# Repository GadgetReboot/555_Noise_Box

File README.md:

# 555_Noise_Box
Dual 555 oscillators with Flip Flop sub-oscillators controlled by MCP42100 digital pots to make sound effects or melodies
<br><br><BR><BR>

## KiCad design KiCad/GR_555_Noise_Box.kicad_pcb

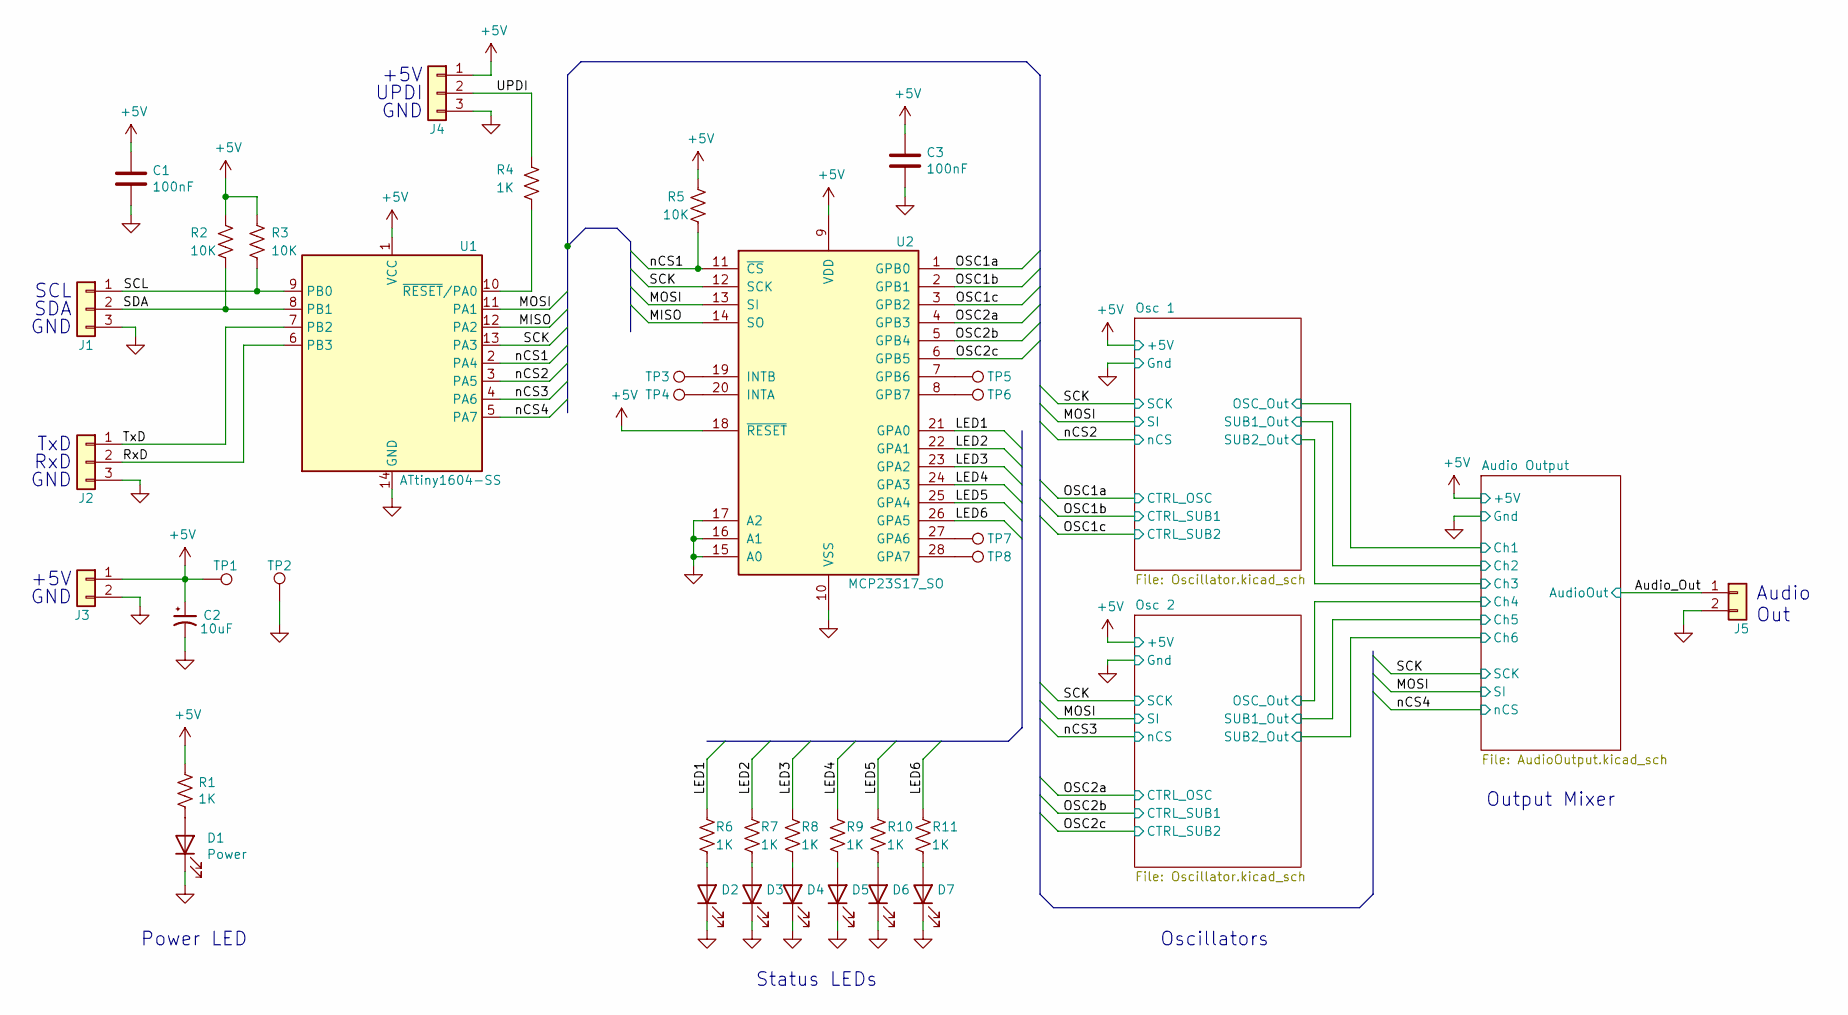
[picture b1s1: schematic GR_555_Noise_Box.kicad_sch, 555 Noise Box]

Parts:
C1, C3: 100nF; C_0805_2012Metric_Pad1.15x1.40mm_HandSolder
C2: 10uF; C_Elec_4x5.8
D1: Power; LED_0805_2012Metric_Pad1.15x1.40mm_HandSolder
D2, D3, D4, D5, D6, D7: LED; LED_0805_2012Metric_Pad1.15x1.40mm_HandSolder
J1, J2, J4: Conn_01x03; PinHeader_1x03_P2.54mm_Vertical_H1.0mm
J3, J5: 1x2; PinHeader_1x02_P2.54mm_Vertical_H1.0mm
R1, R4, R6, R7, R8, R9, R10, R11: 1K; R_0805_2012Metric_Pad1.15x1.40mm_HandSolder
R2, R3, R5: 10K; R_0805_2012Metric_Pad1.15x1.40mm_HandSolder
TP1, TP2: TestPoint; TestPoint_Loop_D2.54mm_Drill1.5mm_Beaded
TP3, TP4, TP5, TP6, TP7, TP8: TestPoint; TestPoint_Pad_D1.0mm
U1: ATtiny1604-SS; SOIC-14_3.9x8.7mm_P1.27mm
U2: MCP23S17_SO; SOIC-28W_7.5x17.9mm_P1.27mm

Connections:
+5V: C1.1, C2.1, C3.1, J3.1, J4.1, R1.1, R2.1, R3.1, R5.1, TP1.1, U1.1 (VCC), U2.9 (VDD), U2.18 (~RESET); also elsewhere on the board
/Audio_Out: J5.1; also elsewhere on the board
/LED1: R6.2, U2.21 (GPA0)
/LED2: R7.2, U2.22 (GPA1)
/LED3: R8.2, U2.23 (GPA2)
/LED4: R9.2, U2.24 (GPA3)
/LED5: R10.2, U2.25 (GPA4)
/LED6: R11.2, U2.26 (GPA5)
/MISO: U1.12 (PA2), U2.14 (SO)
/MOSI: U1.11 (PA1), U2.13 (SI); also elsewhere on the board
/OSC1a: U2.1 (GPB0); also elsewhere on the board
/OSC1b: U2.2 (GPB1); also elsewhere on the board
/OSC1c: U2.3 (GPB2); also elsewhere on the board
/OSC2a: U2.4 (GPB3); also elsewhere on the board
/OSC2b: U2.5 (GPB4); also elsewhere on the board
/OSC2c: U2.6 (GPB5); also elsewhere on the board
/RxD: J2.2, U1.6 (PB3)
/SCK: U1.13 (PA3), U2.12 (SCK); also elsewhere on the board
/SCL: J1.1, R3.2, U1.9 (PB0)
/SDA: J1.2, R2.2, U1.8 (PB1)
/TxD: J2.1, U1.7 (PB2)
/UPDI: J4.2, R4.1
/nCS1: R5.2, U1.2 (PA4), U2.11 (~CS)
/nCS2: U1.3 (PA5); also elsewhere on the board
/nCS3: U1.4 (PA6); also elsewhere on the board
/nCS4: U1.5 (PA7); also elsewhere on the board
GND: C1.2, C2.2, C3.2, D1.1 (K), D2.1 (K), D3.1 (K), D4.1 (K), D5.1 (K), D6.1 (K), D7.1 (K), J1.3, J2.3, J3.2, J4.3, J5.2, TP2.1, U1.14 (GND), U2.10 (VSS), U2.15 (A0), U2.16 (A1), U2.17 (A2); also elsewhere on the board
unnamed: D1.2 (A), R1.2
unnamed: D2.2 (A), R6.1
unnamed: D3.2 (A), R7.1
unnamed: D4.2 (A), R8.1
unnamed: D5.2 (A), R9.1
unnamed: D6.2 (A), R10.1
unnamed: D7.2 (A), R11.1
unnamed: R4.2, U1.10 (~RESET/PA0)
unnamed: TP3.1, U2.19 (INTB)
unnamed: TP4.1, U2.20 (INTA)
unnamed: TP5.1, U2.7 (GPB6)
unnamed: TP6.1, U2.8 (GPB7)
unnamed: TP7.1, U2.27 (GPA6)
unnamed: TP8.1, U2.28 (GPA7)

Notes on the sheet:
UPDI
GND
RxD
Output Mixer
+5V
SDA
Oscillators
Power LED
Status LEDs
TxD
Audio Out
SCL

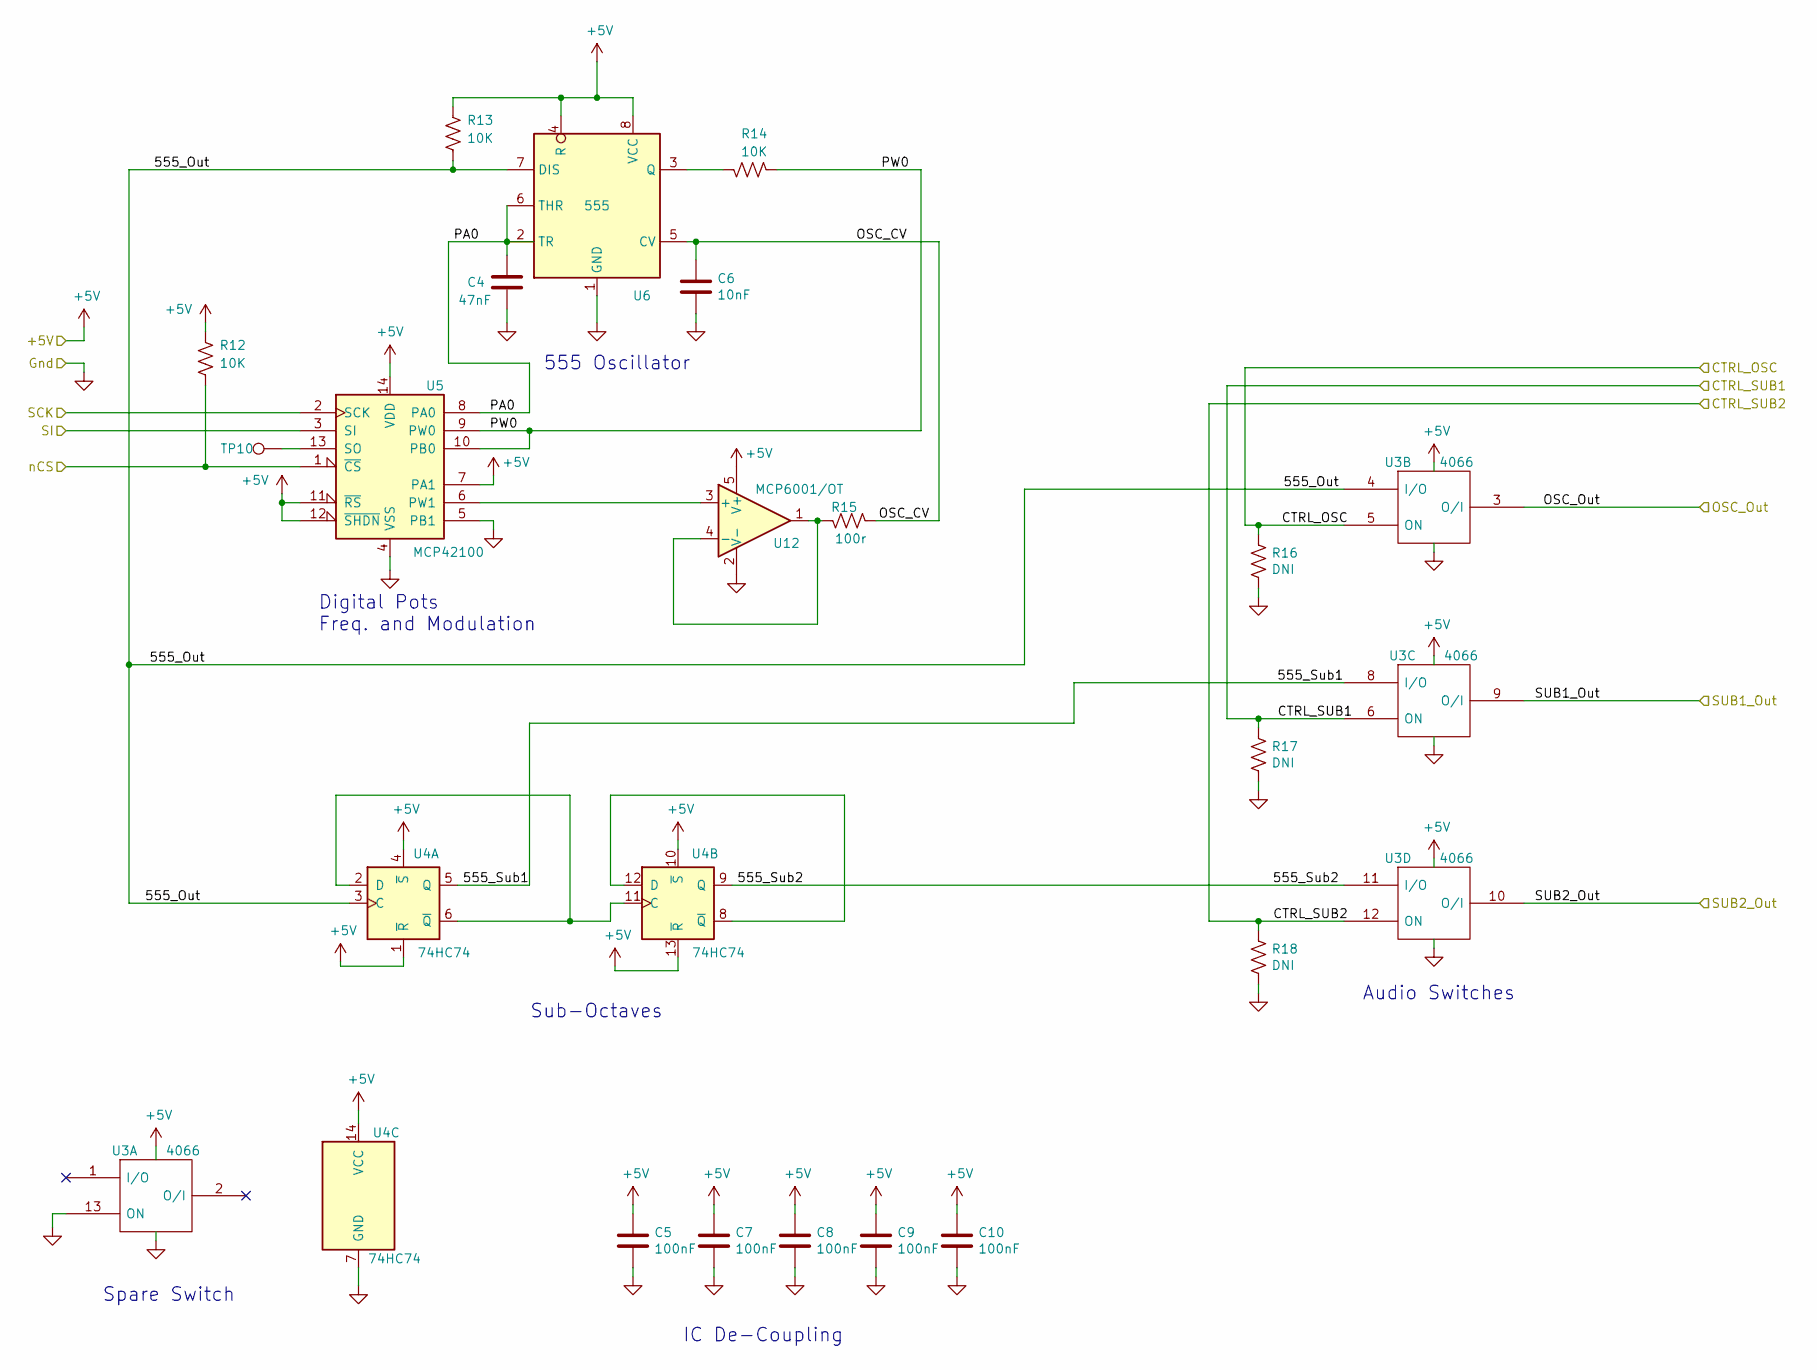
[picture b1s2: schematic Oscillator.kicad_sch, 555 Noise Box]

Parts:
C4: 47nF; C_0805_2012Metric_Pad1.15x1.40mm_HandSolder
C5, C7, C8, C9, C10: 100nF; C_0805_2012Metric_Pad1.15x1.40mm_HandSolder
C6: 10nF; C_0805_2012Metric_Pad1.15x1.40mm_HandSolder
R12, R13, R14: 10K; R_0805_2012Metric_Pad1.15x1.40mm_HandSolder
R15: 100r; R_0805_2012Metric_Pad1.15x1.40mm_HandSolder
R16, R17, R18: DNI; R_0805_2012Metric_Pad1.15x1.40mm_HandSolder
TP10: TestPoint; TestPoint_Pad_D1.0mm
U3: 4066; SOIC-14_3.9x8.7mm_P1.27mm
U4: 74HC74; SOIC-14_3.9x8.7mm_P1.27mm
U5: MCP42100; SOIC-14_3.9x8.7mm_P1.27mm
U6: 555; SOIC-8_3.9x4.9mm_P1.27mm
U12: MCP6001/OT; SOT-23-5

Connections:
+5V: C5.1, C7.1, C8.1, C9.1, C10.1, R12.1, R13.1, U3.14 (Vdd), U4.1 (~R), U4.4 (~S), U4.10 (~S), U4.13 (~R), U4.14 (VCC), U5.7 (PA1), U5.11 (~RS), U5.12 (~SHDN), U5.14 (VDD), U6.4 (R), U6.8 (VCC), U12.5 (V+); also elsewhere on the board
/Audio Output/Ch1: U3.3 (O/I); also elsewhere on the board
/Audio Output/Ch2: U3.9 (O/I); also elsewhere on the board
/Audio Output/Ch3: U3.10 (O/I); also elsewhere on the board
/MOSI: U5.3 (SI); also elsewhere on the board
/OSC1a: R16.1, U3.5 (ON); also elsewhere on the board
/OSC1b: R17.1, U3.6 (ON); also elsewhere on the board
/OSC1c: R18.1, U3.12 (ON); also elsewhere on the board
/Osc 1/555_Out: R13.2, U3.4 (I/O), U4.3 (C), U6.7 (DIS)
/Osc 1/555_Sub1: U3.8 (I/O), U4.5 (Q)
/Osc 1/555_Sub2: U3.11 (I/O), U4.9 (Q)
/Osc 1/OSC_CV: C6.1, R15.2, U6.5 (CV)
/Osc 1/PA0: C4.1, U5.8 (PA0), U6.2 (TR), U6.6 (THR)
/Osc 1/PW0: R14.2, U5.9 (PW0), U5.10 (PB0)
/SCK: U5.2 (SCK); also elsewhere on the board
/nCS2: R12.2, U5.1 (~CS); also elsewhere on the board
GND: C4.2, C5.2, C6.2, C7.2, C8.2, C9.2, C10.2, R16.2, R17.2, R18.2, U3.7 (Vss), U3.13 (ON), U4.7 (GND), U5.4 (VSS), U5.5 (PB1), U6.1 (GND), U12.2 (V-); also elsewhere on the board
unnamed: R14.1, U6.3 (Q)
unnamed: U4.2 (D), U4.6 (~Q), U4.11 (C)
unnamed: U4.8 (~Q), U4.12 (D)

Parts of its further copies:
C11: 47nF; C_0805_2012Metric_Pad1.15x1.40mm_HandSolder
C12, C14, C15, C16, C17: 100nF; C_0805_2012Metric_Pad1.15x1.40mm_HandSolder
C13: 10nF; C_0805_2012Metric_Pad1.15x1.40mm_HandSolder
R19, R20, R21: 10K; R_0805_2012Metric_Pad1.15x1.40mm_HandSolder
R22: 100r; R_0805_2012Metric_Pad1.15x1.40mm_HandSolder
R23, R24, R25: DNI; R_0805_2012Metric_Pad1.15x1.40mm_HandSolder
TP9: TestPoint; TestPoint_Pad_D1.0mm
U7: MCP6001/OT; SOT-23-5
U8: 4066; SOIC-14_3.9x8.7mm_P1.27mm
U9: 74HC74; SOIC-14_3.9x8.7mm_P1.27mm
U10: MCP42100; SOIC-14_3.9x8.7mm_P1.27mm
U11: 555; SOIC-8_3.9x4.9mm_P1.27mm

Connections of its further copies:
+5V: C12.1, C14.1, C15.1, C16.1, C17.1, R19.1, R20.1, U7.5 (V+), U8.14 (Vdd), U9.1 (~R), U9.4 (~S), U9.10 (~S), U9.13 (~R), U9.14 (VCC), U10.7 (PA1), U10.11 (~RS), U10.12 (~SHDN), U10.14 (VDD), U11.4 (R), U11.8 (VCC); also elsewhere on the board
/Audio Output/Ch4: U8.3 (O/I); also elsewhere on the board
/Audio Output/Ch5: U8.9 (O/I); also elsewhere on the board
/Audio Output/Ch6: U8.10 (O/I); also elsewhere on the board
/MOSI: U10.3 (SI); also elsewhere on the board
/OSC2a: R23.1, U8.5 (ON); also elsewhere on the board
/OSC2b: R24.1, U8.6 (ON); also elsewhere on the board
/OSC2c: R25.1, U8.12 (ON); also elsewhere on the board
/Osc 2/555_Out: R20.2, U8.4 (I/O), U9.3 (C), U11.7 (DIS)
/Osc 2/555_Sub1: U8.8 (I/O), U9.5 (Q)
/Osc 2/555_Sub2: U8.11 (I/O), U9.9 (Q)
/Osc 2/OSC_CV: C13.1, R22.2, U11.5 (CV)
/Osc 2/PA0: C11.1, U10.8 (PA0), U11.2 (TR), U11.6 (THR)
/Osc 2/PW0: R21.2, U10.9 (PW0), U10.10 (PB0)
/SCK: U10.2 (SCK); also elsewhere on the board
/nCS3: R19.2, U10.1 (~CS); also elsewhere on the board
GND: C11.2, C12.2, C13.2, C14.2, C15.2, C16.2, C17.2, R23.2, R24.2, R25.2, U7.2 (V-), U8.7 (Vss), U8.13 (ON), U9.7 (GND), U10.4 (VSS), U10.5 (PB1), U11.1 (GND); also elsewhere on the board
unnamed: R21.1, U11.3 (Q)
unnamed: U9.2 (D), U9.6 (~Q), U9.11 (C)
unnamed: U9.8 (~Q), U9.12 (D)

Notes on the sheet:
Audio Switches
Sub-Octaves
Spare Switch
555 Oscillator
Digital Pots Freq. and Modulation
IC De-Coupling

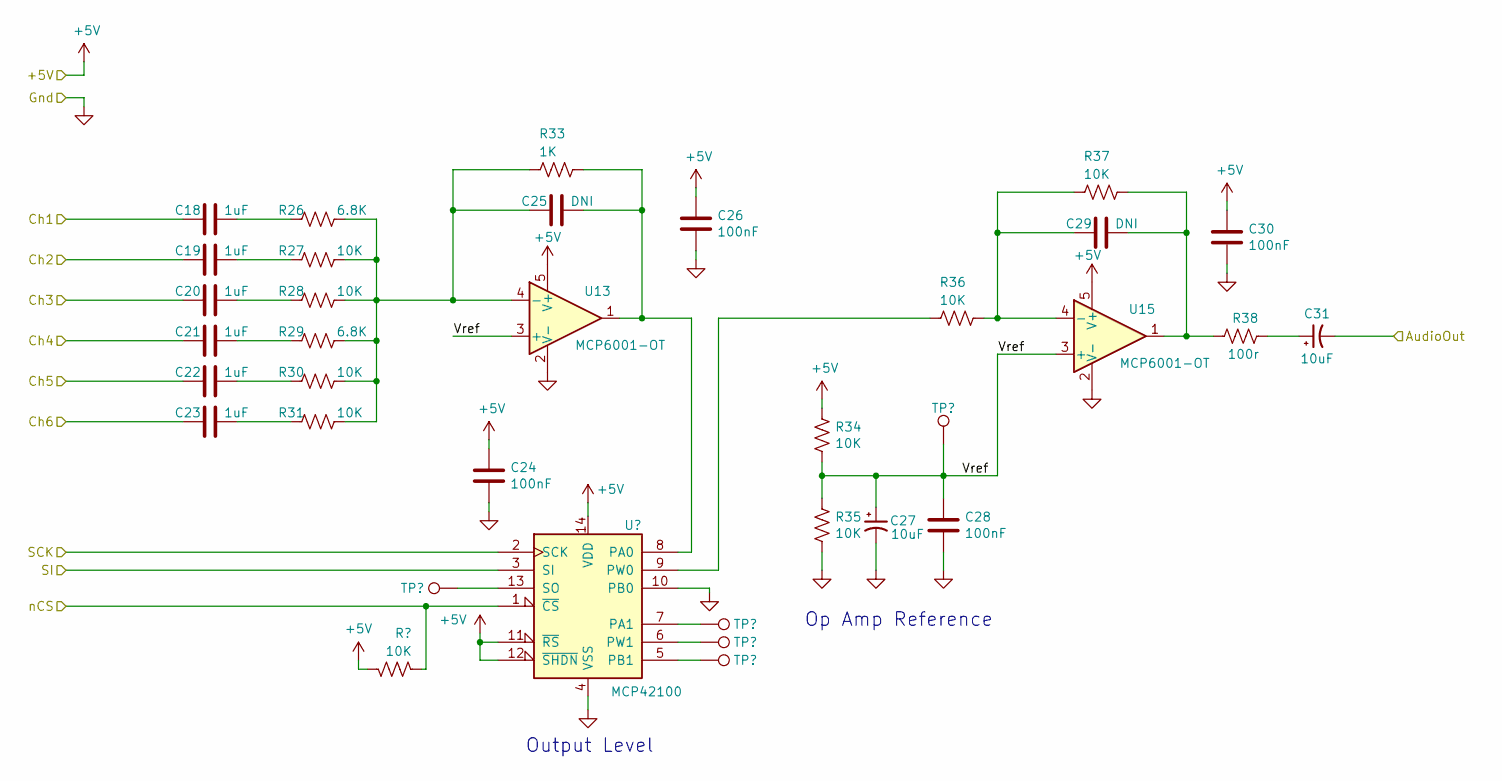
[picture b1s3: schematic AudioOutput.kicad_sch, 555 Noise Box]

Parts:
C18, C19, C20, C21, C22, C23: 1uF; C_0805_2012Metric_Pad1.15x1.40mm_HandSolder
C24, C26, C28, C30: 100nF; C_0805_2012Metric_Pad1.15x1.40mm_HandSolder
C25, C29: DNI; C_0805_2012Metric_Pad1.15x1.40mm_HandSolder
C27, C31: 10uF; C_Elec_4x5.8
R26, R29: 6.8K; R_0805_2012Metric_Pad1.15x1.40mm_HandSolder
R27, R28, R30, R31, R32, R34, R35, R36, R37: 10K; R_0805_2012Metric_Pad1.15x1.40mm_HandSolder
R33: 1K; R_0805_2012Metric_Pad1.15x1.40mm_HandSolder
R38: 100r; R_0805_2012Metric_Pad1.15x1.40mm_HandSolder
TP11, TP12, TP13, TP14, TP15: TestPoint; TestPoint_Pad_D1.0mm
U13, U15: MCP6001-OT; SOT-23-5
U14: MCP42100; SOIC-14_3.9x8.7mm_P1.27mm

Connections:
+5V: C24.1, C26.1, C30.1, R32.1, R34.1, U13.5 (V+), U14.11 (~RS), U14.12 (~SHDN), U14.14 (VDD), U15.5 (V+); also elsewhere on the board
/Audio Output/Ch1: C18.2; also elsewhere on the board
/Audio Output/Ch2: C19.2; also elsewhere on the board
/Audio Output/Ch3: C20.2; also elsewhere on the board
/Audio Output/Ch4: C21.2; also elsewhere on the board
/Audio Output/Ch5: C22.2; also elsewhere on the board
/Audio Output/Ch6: C23.2; also elsewhere on the board
/Audio Output/Vref: C27.1, C28.1, R34.2, R35.1, TP15.1, U13.3 (+), U15.3 (+)
/Audio_Out: C31.2; also elsewhere on the board
/MOSI: U14.3 (SI); also elsewhere on the board
/SCK: U14.2 (SCK); also elsewhere on the board
/nCS4: R32.2, U14.1 (~CS); also elsewhere on the board
GND: C24.2, C26.2, C27.2, C28.2, C30.2, R35.2, U13.2 (V-), U14.4 (VSS), U14.10 (PB0), U15.2 (V-); also elsewhere on the board
unnamed: C18.1, R26.2
unnamed: C19.1, R27.2
unnamed: C20.1, R28.2
unnamed: C21.1, R29.2
unnamed: C22.1, R30.2
unnamed: C23.1, R31.2
unnamed: C25.1, R33.1, U13.1, U14.8 (PA0)
unnamed: C25.2, R26.1, R27.1, R28.1, R29.1, R30.1, R31.1, R33.2, U13.4 (-)
unnamed: C29.1, R37.1, R38.2, U15.1
unnamed: C29.2, R36.1, R37.2, U15.4 (-)
unnamed: C31.1, R38.1
unnamed: R36.2, U14.9 (PW0)
unnamed: TP11.1, U14.13 (SO)
unnamed: TP12.1, U14.7 (PA1)
unnamed: TP13.1, U14.6 (PW1)
unnamed: TP14.1, U14.5 (PB1)

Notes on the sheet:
Output Level
Op Amp Reference

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
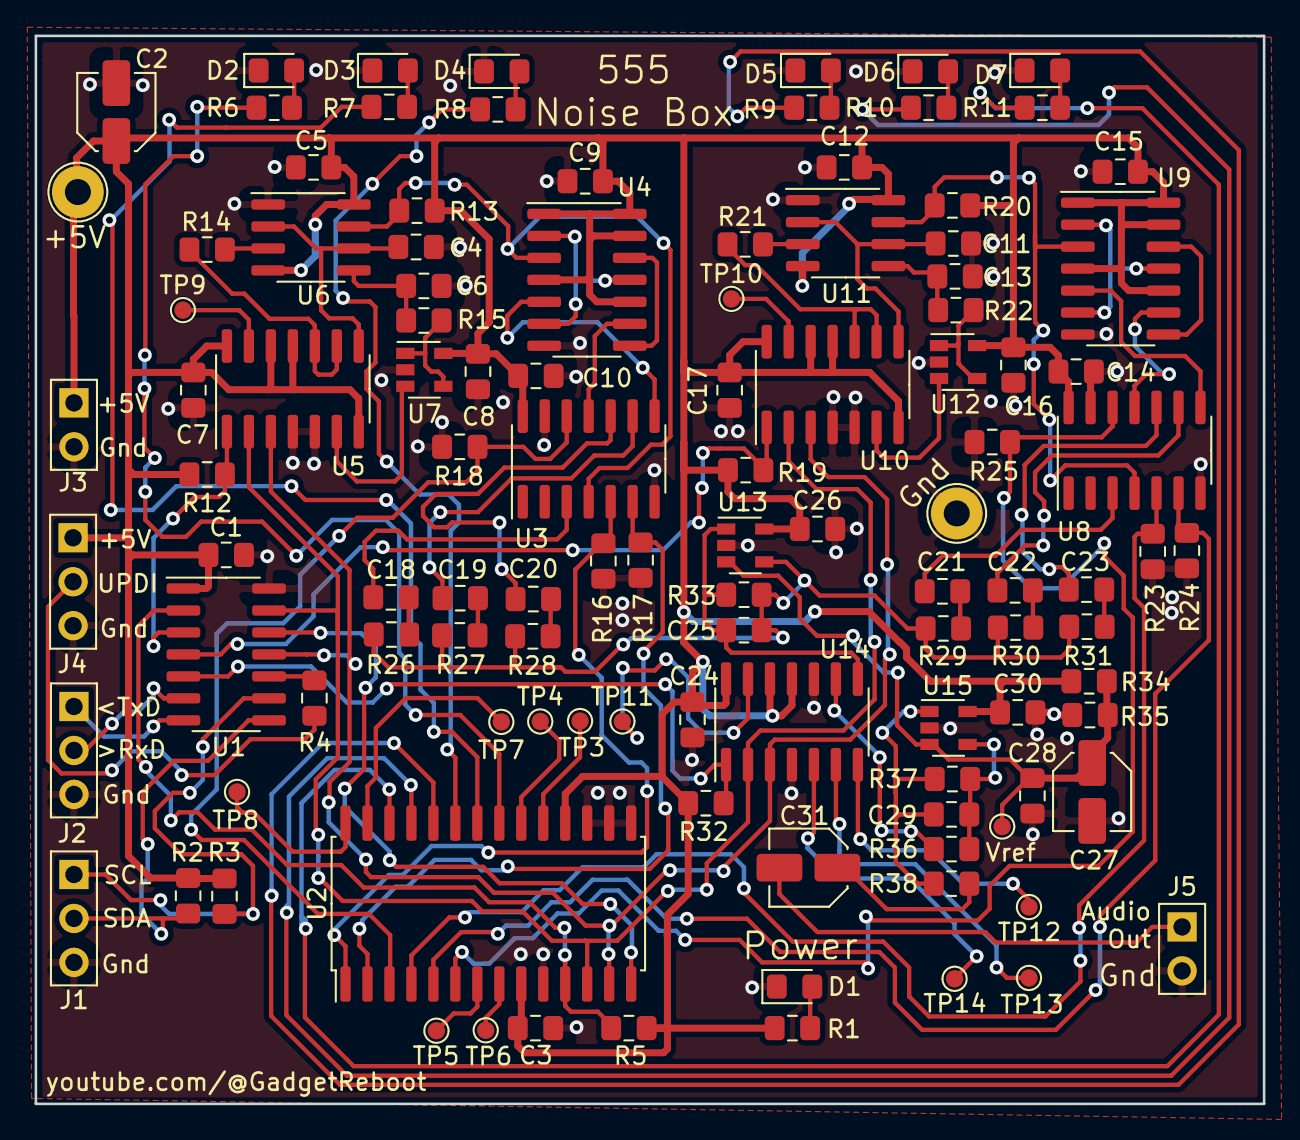
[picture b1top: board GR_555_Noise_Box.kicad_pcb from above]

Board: 2 copper layers, 71.0 x 61.7 mm, 111 parts (0 on the bottom side), 88 nets.

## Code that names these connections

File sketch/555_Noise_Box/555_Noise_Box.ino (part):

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Adafruit_MCP23X17 controllerIO;

// ATTiny1604 GPIO assignment for SPI chip select outputs
const byte nCS1 = 0;  // chip select MCP23s17 GPIO Expander
const byte nCS2 = 1;  // chip select MCP42100 digital pots 555 #1
const byte nCS3 = 2;  // chip select MCP42100 digital pots 555 #2
const byte nCS4 = 3;  // chip select MCP42100 digital pot output volume

// mcp23s17 GPIO assignment
// 555 oscillator paths enabled/disabled
const byte osc1a = 8;   // GPB0  555 #1 Main Osc
const byte osc1b = 9;   // GPB1  555 #1 Sub Octave 1 Osc
const byte osc1c = 10;  // GPB2  555 #1 Sub Octave 2 Osc
const byte osc2a = 11;  // GPB3  555 #2 Main Osc
const byte osc2b = 12;  // GPB4  555 #2 Sub Octave 1 Osc
const byte osc2c = 13;  // GPB5  555 #2 Sub Octave 2 Osc

const byte led1 = 0;  // GPA0
const byte led2 = 1;  // GPA1
const byte led3 = 2;  // GPA2
const byte led4 = 3;  // GPA3
const byte led5 = 4;  // GPA4
const byte led6 = 5;  // GPA5

const byte spare1 = 14;  // GPB6
const byte spare2 = 15;  // GPB7
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  digitalWrite(nCS2, HIGH);  // chip select defaults to de-selected
  digitalWrite(nCS3, HIGH);  // chip select defaults to de-selected
  digitalWrite(nCS4, HIGH);  // chip select defaults to de-selected
  pinMode(nCS2, OUTPUT);     // configure chip select as output
  pinMode(nCS3, OUTPUT);     // configure chip select as output
  pinMode(nCS4, OUTPUT);     // configure chip select as output
  SPI.begin();

  // init mcp23017 and configure GPIO
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  controllerIO.digitalWrite(led5, LOW);
  controllerIO.digitalWrite(led6, LOW);

  controllerIO.pinMode(osc1a, OUTPUT);
  controllerIO.pinMode(osc1b, OUTPUT);
  controllerIO.pinMode(osc1c, OUTPUT);

  controllerIO.pinMode(osc2a, OUTPUT);
  controllerIO.pinMode(osc2b, OUTPUT);
  controllerIO.pinMode(osc2c, OUTPUT);

  controllerIO.pinMode(led1, OUTPUT);
  controllerIO.pinMode(led2, OUTPUT);
  controllerIO.pinMode(led3, OUTPUT);
  controllerIO.pinMode(led4, OUTPUT);
  controllerIO.pinMode(led5, OUTPUT);
  controllerIO.pinMode(led6, OUTPUT);

  controllerIO.pinMode(spare1, INPUT_PULLUP);
  controllerIO.pinMode(spare2, INPUT_PULLUP);
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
